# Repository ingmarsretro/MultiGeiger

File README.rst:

# MultiGeiger (ESP32 WiFi LoRa 32 V2 firmware)

.. image:: docs/Bilder/WiFi_Lora32_V2.jpg
   :alt: MultiGeiger Mainboard for WiFi LorRa 32 V2

This repository contains a **MultiGeiger** firmware build targeting the **Heltec WiFi LoRa 32 V2** (ESP32 + OLED + LoRa) and a matching hardware pinout. MultiGeiger is a **radioactivity measurement device** (Geiger‑Müller tube + HV supply) that can display measurements locally and publish them to community services.

- **Firmware location**: `MultiGeiger-master/` (PlatformIO project)
- **Online documentation (EN/DE, versioned)**: `https://multigeiger.readthedocs.org/`
- **Map / Karte**: `https://multigeiger.citysensor.de/`

---

## English

### What is MultiGeiger?

MultiGeiger measures Geiger‑Müller tube pulses, calculates **CPM** (counts per minute) and derived dose rates (depending on tube type), and can:

- show current / accumulated values on an OLED
- tick on every pulse (speaker + LED)
- send measurements to:
  - **sensor.community** (archive)
  - **madavi.de** (near real-time graphs)
  - **TTN (LoRaWAN)** (for LoRa boards)
  - **MQTT** (local broker / home automation)

Temperature / humidity / pressure sensors **BME280 / BME680** are supported (optional).

### Hardware target and pinout (Heltec WiFi LoRa 32 V2)

This build is configured for the Heltec board environment `wifi_lora_32_v2`. The intended pin mapping is documented in `MultiGeiger-master/platformio.ini`:

- **I²C**: SDA = GPIO4, SCL = GPIO15
- **GM pulse input**: GPIO2 (`GMZ_COUNT`)
- **HV / charging**: GPIO22 (`HV_CAP_FUL`), GPIO23 (`HV_FET_OUT`)
- **Speaker**: GPIO0 + GPIO13
- **DIP switches**: GPIO39/38/37/36 (SW0..SW3)

DIP switches (closed to GND = ON) are read at runtime in the loop:

- **SW0**: speaker tick enable
- **SW1**: display enable
- **SW2**: LED tick enable
- **SW3**: BLE enable

### Build and flash (PlatformIO)

This is a PlatformIO project (`MultiGeiger-master/platformio.ini`) using:

- platform `espressif32`
- framework `arduino`
- board `heltec_wifi_lora_32_V2`

Open `MultiGeiger-master/` in PlatformIO and build/upload the `wifi_lora_32_v2` environment.

### Configuration (WiFi, servers, LoRa, MQTT, OTA)

MultiGeiger provides a web configuration UI and **OTA firmware update**:

- The device advertises an AP with an SSID like `ESP32-<chipid>` (built from the ESP32 MAC).
- In **full config mode**, the config page supports toggles for:
  - display / speaker / LED tick
  - send to sensor.community / madavi / TTN (LoRa) / BLE / MQTT
  - LoRaWAN keys (DEVEUI / APPEUI / APPKEY) when LoRa hardware is present
  - MQTT broker / port / topic
  - optional local alarm threshold + factor

**AP password note**:  (see `MultiGeiger-master/multigeiger/webconf.cpp`, `wifiInitialApPassword`). 

### Data formats (MQTT)

If MQTT is enabled and configured, the firmware publishes a JSON payload like:

```json
{"usv_h":0.0123,"cpm":17,"usv_h_since_start":0.0101,"version":"V2.0.0"}
```

Topic and broker/port are configurable in the web UI.

### “Final version” changes in this repository

Compared to a plain upstream build, this repo includes/uses several stability and deployment changes (visible in source and build flags):

- **Crash-avoidance for WiFi/AP + web config**:
  - Optional **minimal WiFi mode** controlled by `MULTIGEIGER_MINIMAL_WIFI` (build flag). In this mode, the firmware starts a basic AP + web server without full IotWebConf init, to avoid a known crash scenario on this target.
  - In normal mode (`MULTIGEIGER_MINIMAL_WIFI=0`), `IotWebConf.init()` is executed in a dedicated FreeRTOS task with a large stack to reduce stack/overflow issues during AP mode transitions.
  - The main loop task stack is increased (`SET_LOOP_TASK_STACK_SIZE(16 * 1024)`) to avoid “LoadProhibited” failures around AP mode / configuration.
- **HV recharge and audio moved away from ISR flash calls**:
  - Controlled by `MULTIGEIGER_RECHARGE_FROM_TASK=1`. Recharge (and related ticking) is run from a task; timer ISR only wakes the task. This avoids exceptions when ISR paths would otherwise call code located in flash.
- **MQTT uplink support**:
  - Optional MQTT publish via `PubSubClient`, configurable from the web UI (broker/port/topic).

### License

MultiGeiger is licensed under **GNU GPL v3 (or later)**. See `MultiGeiger-master/LICENSE`.

---

## Deutsch

### Was ist MultiGeiger?

MultiGeiger misst die Impulse eines Geiger‑Müller‑Zählrohrs, berechnet **CPM** (Counts per Minute) sowie abgeleitete Dosisleistungen (abhängig vom Röhrentyp) und kann:

- Messwerte lokal auf einem OLED anzeigen
- bei jedem Impuls ticken (Lautsprecher + LED)
- Messdaten senden an:
  - **sensor.community** (Archiv)
  - **madavi.de** (nahezu Echtzeit‑Graphen)
  - **TTN (LoRaWAN)** (bei LoRa‑Boards)
  - **MQTT** (lokaler Broker / Smart‑Home)

Optional werden **BME280 / BME680** (Temperatur/Luftfeuchte/Luftdruck) unterstützt.

### Hardware-Ziel und Pinbelegung (Heltec WiFi LoRa 32 V2)

Dieses Build ist für die PlatformIO‑Umgebung `wifi_lora_32_v2` ausgelegt. Die vorgesehene Pinbelegung steht in `MultiGeiger-master/platformio.ini`:

- **I²C**: SDA = GPIO4, SCL = GPIO15
- **GM‑Impuls Eingang**: GPIO2 (`GMZ_COUNT`)
- **HV / Laden**: GPIO22 (`HV_CAP_FUL`), GPIO23 (`HV_FET_OUT`)
- **Lautsprecher**: GPIO0 + GPIO13
- **DIP‑Schalter**: GPIO39/38/37/36 (SW0..SW3)

DIP‑Schalter (gegen GND geschlossen = EIN) werden im Loop ausgewertet:

- **SW0**: Lautsprecher‑Tick
- **SW1**: Display EIN/AUS
- **SW2**: LED‑Tick
- **SW3**: BLE EIN/AUS

### Build und Flashen (PlatformIO)

PlatformIO‑Projekt: `MultiGeiger-master/platformio.ini` mit:

- Platform `espressif32`
- Framework `arduino`
- Board `heltec_wifi_lora_32_V2`

Öffne `MultiGeiger-master/` in PlatformIO und baue/flash die Umgebung `wifi_lora_32_v2`.

### Konfiguration (WLAN, Server, LoRa, MQTT, OTA)

MultiGeiger bietet eine Web‑Konfiguration sowie **OTA‑Firmware‑Updates**:

- Das Gerät erzeugt einen Access Point mit SSID `ESP32-<chipid>` (aus der ESP32‑MAC abgeleitet).
- Im **vollständigen Konfigurationsmodus** lassen sich u. a. einstellen:
  - Display / Lautsprecher / LED Tick
  - Senden an sensor.community / madavi / TTN (LoRa) / BLE / MQTT
  - LoRaWAN‑Schlüssel (DEVEUI / APPEUI / APPKEY) bei vorhandener LoRa‑Hardware
  - MQTT Broker / Port / Topic
  - optionaler lokaler Alarm (Schwelle + Faktor)

**Hinweis zum AP‑Passwort**: (siehe `MultiGeiger-master/multigeiger/webconf.cpp`, `wifiInitialApPassword`). 

### Datenformat (MQTT)

Wenn MQTT aktiviert und konfiguriert ist, wird ein JSON‑Payload publiziert, z. B.:

```json
{"usv_h":0.0123,"cpm":17,"usv_h_since_start":0.0101,"version":"V2.0.0"}
```

Topic sowie Broker/Port sind über die Web‑UI konfigurierbar.

### Änderungen in der „Final Version“ dieses Repos

Dieses Repo enthält (sichtbar im Quellcode und den Build‑Flags) mehrere Änderungen für Stabilität und Deployment:

- **Stabilität bei WiFi/AP + Web‑Konfiguration**:
  - Optionaler **Minimal‑WiFi‑Modus** via `MULTIGEIGER_MINIMAL_WIFI` (Build‑Flag). In diesem Modus wird ein einfacher AP + Webserver‑Setup ohne vollständige IotWebConf‑Initialisierung gestartet, um einen bekannten Crash‑Pfad zu vermeiden.
  - Im Normalbetrieb (`MULTIGEIGER_MINIMAL_WIFI=0`) läuft `IotWebConf.init()` in einem eigenen FreeRTOS‑Task mit großem Stack, um Stack‑Probleme beim Wechsel in den AP‑Modus zu reduzieren.
  - Erhöhter Stack für den Loop‑Task (`SET_LOOP_TASK_STACK_SIZE(16 * 1024)`), um “LoadProhibited”‑Fehler zu vermeiden.
- **HV‑Nachladen und Audio weg aus ISR‑Flash‑Pfaden**:
  - Gesteuert über `MULTIGEIGER_RECHARGE_FROM_TASK=1`. Das Nachladen läuft in einem Task; die Timer‑ISR weckt nur den Task. Das reduziert Exceptions, wenn ISR‑Code sonst Flash‑Code aufrufen würde.
- **MQTT‑Uplink**:
  - Optionales MQTT‑Publishing via `PubSubClient`, konfigurierbar in der Web‑UI (Broker/Port/Topic).

### Lizenz

MultiGeiger steht unter der **GNU GPL v3 (oder neuer)**. Siehe `MultiGeiger-master/LICENSE`.

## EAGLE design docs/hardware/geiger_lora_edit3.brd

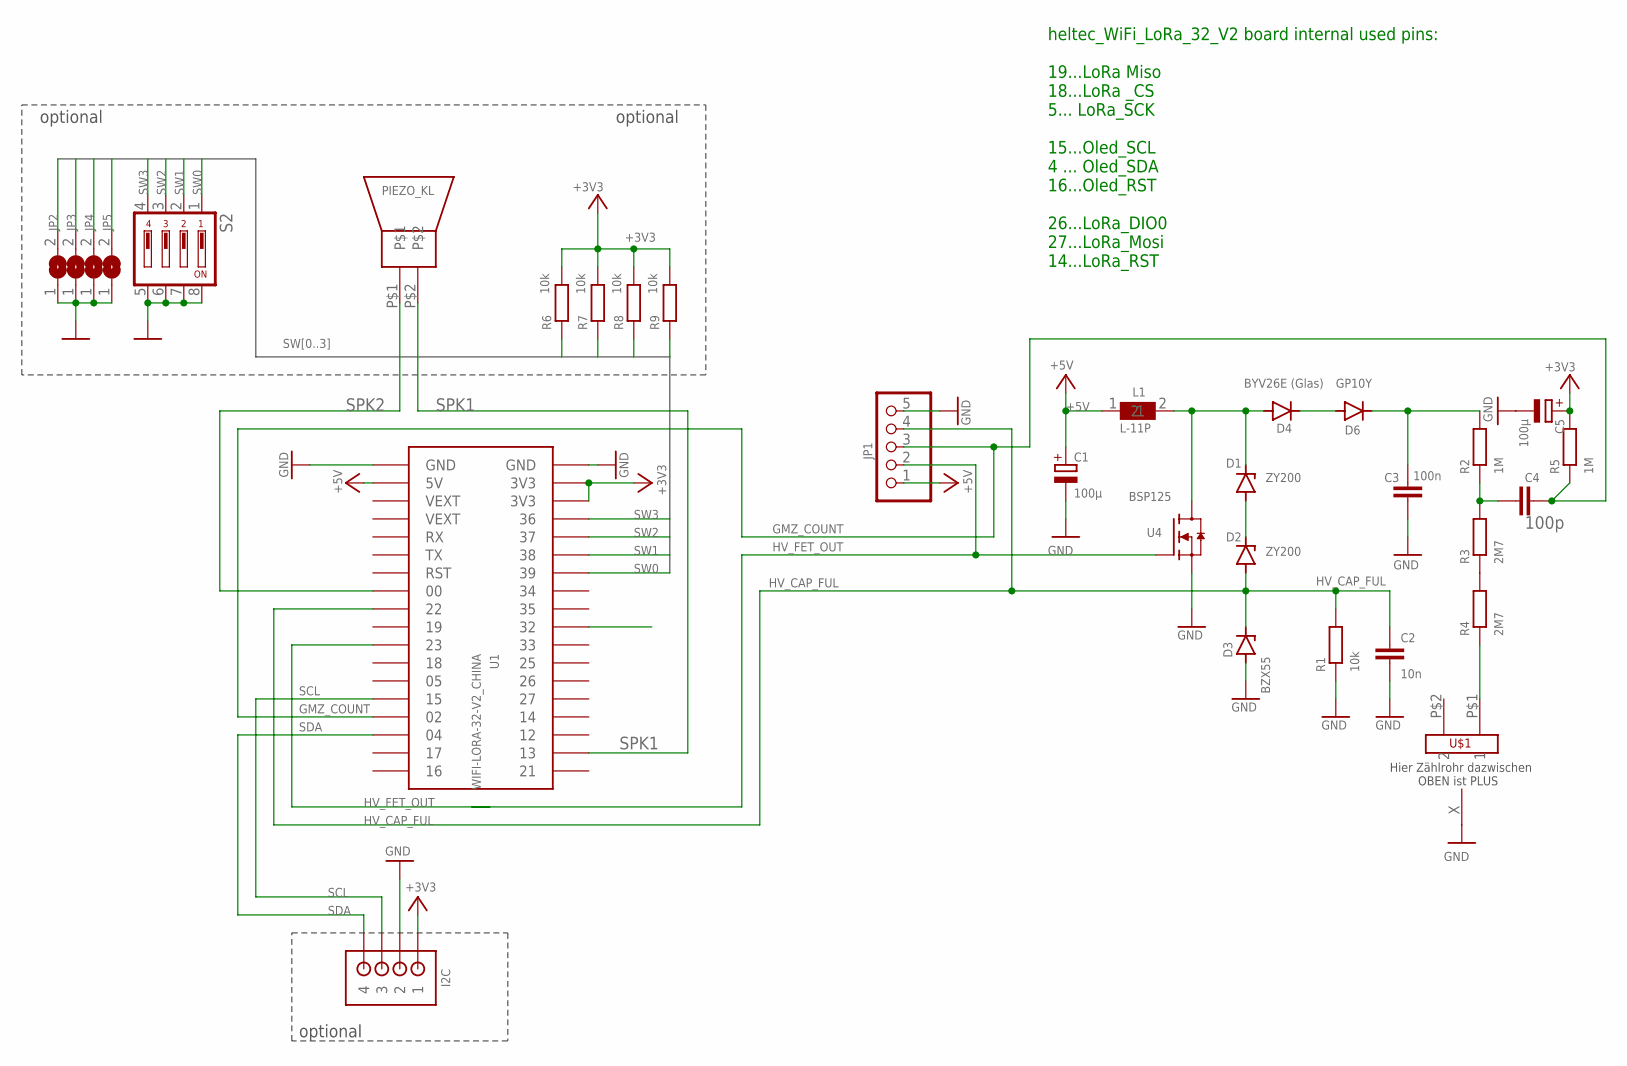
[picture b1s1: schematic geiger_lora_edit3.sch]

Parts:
C1, C5: 100µ; E2-5
C2: 10n; C050-035X075
C3: 100n; C150-072X183
C4: 100p; C050-045X075
D1, D2: ZY200; DO41Z10
D3: BZX55; DO35Z10
D4: BYV26E (Glas); DO41-10
D6: GP10Y; DO41-10
I2C: B4B-ZRSIDE_ENTRY; S4B-ZR
JP1: PINHD-1X5; 1X05
JP2: Jumper; SJ
JP3, JP4, JP5: SJ
L1: L-11P
PIEZO_KL: PIEPSER
R1: 10k; 0207/10
R2, R5: 1M; 0207/10
R3, R4: 2M7; 0207/10
R6, R7, R8, R9: 10k; M0805
S2: DIP04YL
U1: WIFI-LORA-32-V2_CHINA; 2.54MM_2X18_CHINA
U4: BSP125; SOT223
U$1: FUSE_HOLDER
U$5: ONE_PAD

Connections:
+3V3: C5.+, I2C.1, R5.2, R6.2, R7.2, R8.2, R9.2, U1.P$34 (3V3), U1.P$35 (3V3)
+5V: C1.+, JP1.1, L1.1, U1.P$2 (5V)
GMZ_COUNT: C4.2, JP1.3, R5.1, U1.P$15 (02)
GND: C1.-, C2.2, C3.2, C5.-, D3.A, I2C.2, JP1.5, JP2.1, JP3.1, JP4.1, JP5.1, R1.1, S2.5, S2.6, S2.7, S2.8, U1.P$1 (GND), U1.P$36 (GND), U4.3 (S), U$5.X
HV_CAP_FUL: C2.1, D2.A, D3.C, JP1.4, R1.2, U1.P$9 (22)
HV_FET_OUT: JP1.2, U1.P$11 (23), U4.1 (G)
unnamed: D1.A, D2.C
unnamed: D1.C, D4.A, L1.2, U4.2 (D), U4.4 (D)
unnamed: C3.1, D6.C, R2.2
unnamed: R4.1, U$1.P$1 (1)
unnamed: R3.1, R4.2
unnamed: C4.1, R2.1, R3.2
unnamed: D4.C, D6.A
SCL: I2C.3, U1.P$14 (15)
SDA: I2C.4, U1.P$16 (04)
SPK1: PIEZO_KL.P$2, U1.P$20 (13)
SPK2: PIEZO_KL.P$1, U1.P$8 (00)
SW0: JP5.2, R6.1, S2.1, U1.P$30 (39)
SW1: JP4.2, R7.1, S2.2, U1.P$31 (38)
SW2: JP3.2, R8.1, S2.3, U1.P$32 (37)
SW3: JP2.2, R9.1, S2.4, U1.P$33 (36)

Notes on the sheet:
Hier Zählrohr dazwischen OBEN ist PLUS
optional
heltec_WiFi_LoRa_32_V2 board internal used pins: 19...LoRa Miso 18...LoRa _CS 5... LoRa_SCK 15...Oled_SCL 4 ... Oled_SDA 16...Oled_RST 26...LoRa_DIO0 27...LoRa_Mosi 14...LoRa_RST

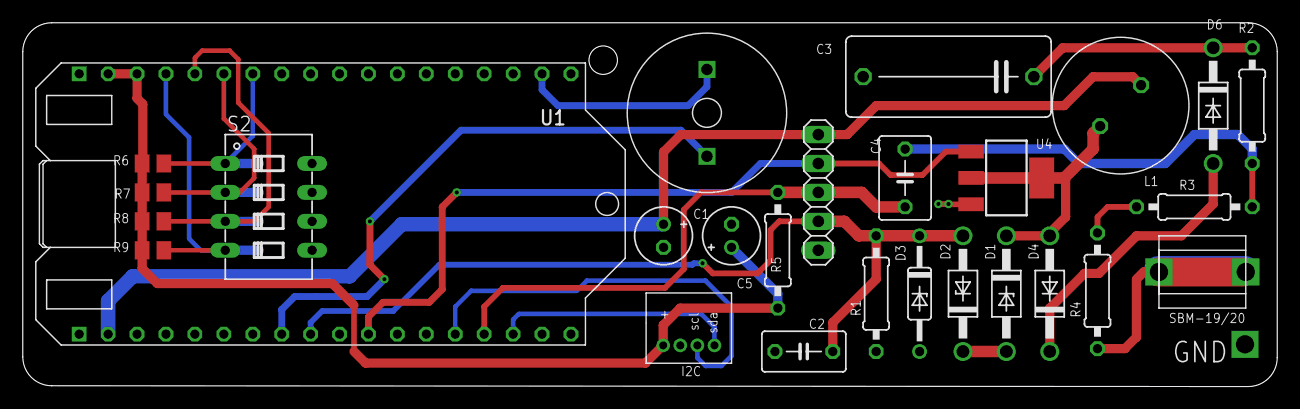
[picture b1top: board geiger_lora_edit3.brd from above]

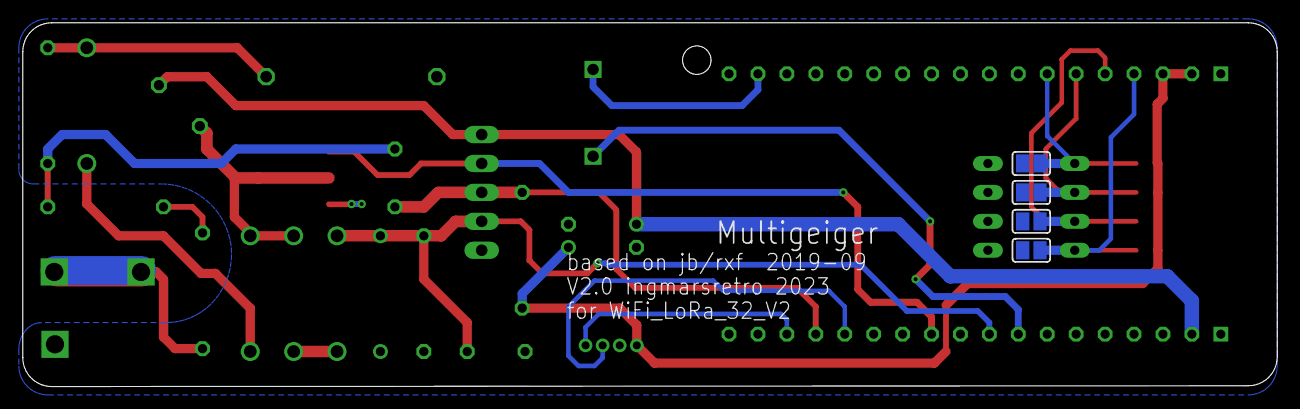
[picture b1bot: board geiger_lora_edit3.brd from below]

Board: 2 copper layers, 110.1 x 31.9 mm, 32 parts (4 on the bottom side), 21 nets.

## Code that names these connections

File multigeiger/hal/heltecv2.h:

// clang-format off
// upload_speed 921600
// board heltec_wifi_lora_32_V2 (Wifi_LorA-32_V2)
//
// Wifi_LorA-32_V2 pinout used in this project:
//   pin4  = SDA (I2C/OLED),  pin15 = SCL (I2C/OLED)
//   pin2  = GMZ_COUNT,       pin22 = HV_CAP_FUL,  pin23 = HV_FET_OUT
//   pin0  = Speaker pin1,    pin13 = Speaker pin2
//   pin39 = sw0, pin38 = sw1, pin37 = sw2, pin36 = sw3

#ifndef _HELTECV2_H
#define _HELTECV2_H

#include <stdint.h>

// Hardware related definitions for Heltec V2 LoRa-32 Board (Wifi_LorA-32_V2)

//#define HAS_BME 1 // Enable BME sensors in general
//#define HAS_BME680 GPIO_NUM_4, GPIO_NUM_15 // SDA, SCL
//#define BME680_ADDR BME680_I2C_ADDR_PRIMARY // connect SDIO of BME680 to GND

#define HAS_LORA 1       // comment out if device shall not send data via LoRa
#define CFG_sx1276_radio 1

#define HAS_DISPLAY U8X8_SSD1306_128X64_NONAME_HW_I2C // OLED-Display on board
#define HAS_LED NOT_A_PIN
// #define HAS_LED LED_BUILTIN                           // white LED on board
#define HAS_BUTTON KEY_BUILTIN                        // button "PROG" on board

//#define BAT_MEASURE_ADC ADC2_GPIO13_CHANNEL  // battery probe GPIO pin
//#define BAT_VOLTAGE_DIVIDER 4 // voltage divider 220k/100k on board
// Vext = GPIO21 on Wifi_LorA-32_V2 (OLED/external power, LOW = on). Override board if wrong.
#undef Vext
#define Vext 21
#define EXT_POWER_SW Vext // switches battery power, Vext control 0 = on / 1 = off
#define EXT_POWER_ON    0
//#define EXT_POWER_OFF   1

// Pins for I2C interface of OLED Display
#define MY_OLED_SDA SDA_OLED
#define MY_OLED_SCL SCL_OLED
#define MY_OLED_RST RST_OLED

// Pins for LORA chip SPI interface come from board file, we need some
// additional definitions for LMIC
#define LORA_IRQ DIO0
#define LORA_IO1 DIO1
#define LORA_IO2 DIO2
#define LORA_SCK SCK
#define LORA_MISO MISO
#define LORA_MOSI MOSI
#define LORA_RST RST_LoRa
#define LORA_CS SS

#endif

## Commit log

2026-03-30 Add files via upload
    MultiGeiger-master/multigeiger/display.cpp
    Reintroduced proper display visibility control.
    Added display_set_visible() / display_is_visible().
    Implemented OLED power switching via Vext (off = HIGH, on = LOW on this board).
    Blocked all OLED drawing when display is disabled (g_display_visible guard).
    MultiGeiger-master/multigeiger/display.h
2026-03-30 Add files via upload
    MultiGeiger-master/multigeiger/multigeiger.ino
    Applied display on/off state every loop via display_set_visible(effective_display_on).
    In setup: reload switches/config state and apply display visibility immediately after web config load.
    Updated speaker setup and runtime tick handling to remove LED tick dependency.
    Updated DIP switch comment: SW2 marked as unused for tick control.
    MultiGeiger-master/multigeiger/multigeiger.ino
2026-03-30 Add files via upload
    MultiGeiger-master/multigeiger/speaker.cpp
    Removed LED-tick feature from tick generation logic.
    Kept speaker tick logic (software setting + SW0).
    Added startup sound sequence and play on boot when playSound is enabled.
    Kept safe idle/silent speaker output behavior.
    MultiGeiger-master/multigeiger/speaker.h
2026-03-30 Add files via upload
    MultiGeiger-master/multigeiger/webconf.cpp
    Removed LED tick option from config page/UI and runtime config variables.
    Kept start sound, speaker tick, display, BLE, MQTT, LoRa, alarm options.
    Bumped config layout version from 016 to 017 (storage layout changed).
    MultiGeiger-master/multigeiger/webconf.h
    Removed extern bool ledTick;
2026-03-30 Add files via upload
    MultiGeiger-master/multigeiger/userdefines.h
    Removed LED_TICK default define.
    MultiGeiger-master/multigeiger/userdefines-example.h
    Removed LED_TICK example define.
    MultiGeiger-master/multigeiger/userdefines.h
    LED_TICK Default-Define entfernt.
2026-03-30 Add files via upload
    MultiGeiger-master/multigeiger/switches.cpp
    Updated debug text: SW2 is now logged as unused for tick behavior.
    MultiGeiger-master/multigeiger/switches.cpp
    Debug-Text angepasst: SW2 wird als unbenutzt für Tick-Verhalten geloggt.
2026-03-30 Add files via upload
    MultiGeiger-master/multigeiger/hal/heltecv2.h
    Set onboard LED pin definition to GPIO25 (HAS_LED 25) for Heltec WiFi LoRa 32 V2.
    ultiGeiger-master/multigeiger/hal/heltecv2.h
    Onboard-LED-Pin für Heltec WiFi LoRa 32 V2 auf GPIO25 gesetzt (HAS_LED 25).
